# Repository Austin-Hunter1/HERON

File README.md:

# HERON

## Cloning

This repository uses git submodules. To pull everything, including submodule contents, clone with:

```bash
git clone --recurse-submodules https://github.com/Austin-Hunter1/HERON.git
```

If you already cloned without that flag, run:

```bash
git submodule update --init
```

## Submodules

- [gps-tracking-example](gps-tracking-example) — linked from [cu-sense-lab/gps-tracking-example](https://github.com/cu-sense-lab/gps-tracking-example) (upstream reference; HERON's working copy is `gnss_processing/`)
- [gnss_processing/submodules/gnss-tools](gnss_processing/submodules/gnss-tools) — linked from [cu-sense-lab/gnss-tools](https://github.com/cu-sense-lab/gnss-tools), used by `gnss_processing/`
- [HERON_WRITING](HERON_WRITING) — reports and papers, linked from [Austin-Hunter1/HERON_WRITING](https://github.com/Austin-Hunter1/HERON_WRITING)

## Where things are

- `HERON_DEPLOY_SOFTWARE/` — the flight computer and ground station software (see its `README.md`).
- `gnss_processing/` — the post-processing tools.
- `docs/` — project documents; start with `docs/GETTING_STARTED.md`.
- `SURGE/` — the 2022 predecessor project, reference only.

## GNSS Processing

[gnss_processing](gnss_processing) is HERON's own working copy of `gps-tracking-example`
(notebooks and code edits for the UAS GNSS-R tracking pipeline — reacquisition after
data-drop overflows, navigation-message decoding across a stitched run, and related
fixes) kept as a plain folder here rather than a submodule, since this project does not
have push access to `cu-sense-lab/gps-tracking-example`. See its own
[README](gnss_processing/README.md) for what differs from upstream.

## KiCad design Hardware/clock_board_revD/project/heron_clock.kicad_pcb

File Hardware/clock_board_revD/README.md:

# HERON clock board (rev D): 10 MHz + PPS distribution, jacks on the real SDR connectors

Rev D puts each jack on the SDR connector it must mate with (D-094). The rev C jacks faced the
wrong SMAs (see Q-015 b): the SDR rear edge order is **GPS ANT, 10 MHz, USB-B, PPS, DC jack**
(silkscreen on a B210 and a B200, photos 2026-10-20). The USB-B connector sits between the
10 MHz and PPS SMAs, so the board is taller and has a hole for each USB plug.

**Status: ready to order (D-101). Not ordered. Not built.** The SDR connector positions, the
USB hole size and the plug clearances are checked on the real parts (user, 2026-10-27).

The circuit, the schematic and the parts are the rev C ones, including the JST XH power
connector J1 (D-092) and the Panjit SOD-323HE land for D2 (D-093). One part change (D-097): the 10 MHz ESD diodes D4–D7 are the bidirectional TPD1E10B06DYAR
(same SOD-523 package), because the AC-coupled 10 MHz swings below GND.

## What changed from rev C

| Item | Rev C | Rev D |
| --- | --- | --- |
| Board | 118 × 44 mm, rack z 10 to 54 | 118 × 60 mm, rack z 30 to 90 |
| 10 MHz jacks J3–J6 | Faced the SDR GPS ANT SMA (wrong) | Face the SDR 10 MHz SMA (bx 34.16), rack z 43.16 |
| PPS jacks J7–J10 | Faced the SDR 10 MHz SMA (wrong) | Face the SDR PPS SMA (bx 70.89), rack z 79.89 |
| USB-B | Plug above the board | Plug through a 16 × 18 mm hole in the board; the B200_2 hole is an open notch |
| SDR GPS ANT and DC jack | GPS ANT covered by the board | Both stay free for cables: the board stays above the GPS ANT plug and below the DC plug |
| Layout | Rev B layout, patched by `make_revc.py` | New: `gen_pcb.py` places all parts and routes the sensitive nets by hand; Freerouting routes the rest (as rev B) |
| Footprints | KiCad 7 copies (25 `lib_footprint_mismatch` notes) | Loaded from the KiCad 10 library and the project library: no mismatch |
| PPS outputs | Dog-leg around a jack leg (3 starved thermals, D-091) | ESD diode and 22 R straight right of the jack tab: no starved thermals |
| 10 MHz filter columns | Right of the jack | Left of the jack (mirror image of rev C); the jack turns 180° so its tab points at the column |
| DRC | 28 items (accepted) | **0 violations, 0 unconnected, 0 footprint errors, 0 schematic parity issues** |

## Geometry

All numbers come from `revd_geom.py`. Board-local coordinates: mm, (0, 0) = top-left corner seen
from the component side (the side that faces the SDRs). Rack: world X = 46 + x, world Z = 90 − y.

| SDR | PPS jack (y 10.11) | USB hole (x0..x1, y 20.31..38.31) | 10 MHz jack (y 46.84) |
| --- | --- | --- | --- |
| B210_1 | J7 (13.16) | 11.05..27.05 | J3 (13.16) |
| B210_2 | J8 (43.16) | 41.05..57.05 | J4 (43.16) |
| B200_1 | J9 (73.16) | 71.05..87.05 | J5 (73.16) |
| B200_2 | J10 (103.16) | 101.05..118 (notch) | J6 (103.16) |

- **USB holes:** 16 mm (x) × 18 mm (y), 1 mm corner radius, centred 5.89 mm right of the jack axis
  (the USB-B axis is 5.89 mm from the SMA axis, toward the SDR component side). Sized for a generic
  straight USB 3.0 B overmold of 16 × 14 mm with 1 mm clearance. Checked with the real cable (D-101).
- **Keep-out ring:** 2 mm round each hole, on all four copper layers: no tracks, vias, pads,
  pours or parts. A hole can grow to about 20 × 22 mm by an Edge.Cuts change only.
- **Board edges:** the top edge (rack z 90) is 8.4 mm below the SDR DC jack axis (z 98.4); the
  bottom edge (z 30) is 6.8 mm above the GPS ANT axis (z 23.2). A plug up to about 13 mm in
  diameter fits on each. Checked with the real plugs (D-101).
- **Mounting holes:** 6 × M3, all 4 mm in from the long edges. H1–H4 at the corners: rack (X, Z) = (50, 86), (160, 86),
  (50, 34), (160, 34). H5, H6 (D-095) at the middle of the top and bottom edges, in line with the corner holes:
  (105, 86) and (105, 34). They carry the push of the direct-mate jacks when the SDR trays slide in. At X 105
  the rear plate is solid (between the B210_2 and B200_1 solder windows), so each standoff seats on full material.
- **J1** (JST XH): mouth on the top edge between the B210_1 and B210_2 DC plugs.
- **J2** (PPS IN, SMA): in the gap between the B200_1 and B200_2 blades, so a cable on J2 has open
  space in front of the board, as in rev C.

## Layout

- **10 MHz filter columns:** the rev C column, mirrored, on the line 7.5 mm left of each 10 MHz jack.
  The series parts are 0 R, 100 nF, 820 nH, 820 nH, 17.4 R and the last 294 R (to GND); the shunt
  parts stand beside the line (`SERIES_DY`, `SHUNTS` in `gen_pcb.py`). Each GND pad has its own via.
- **PPS outputs:** jack tab (+x) → node track → TPD1E05U06 pin 1 (GND pin below, with a via) →
  22 R lying flat, pin 2 on the node.
- **Blocks:** power input left of J8 at the top (rev C positions); LDOs under the B210_1 hole (the rev C
  block moved as one piece); TCXO U3 and LMK1C1104 U4 under the B210_2 hole; PPS buffer U6 right of J8;
  PPS input (U5, J2) between the B200 blades.
- **U3 rules (SiT5155 layout guide):** supply via → C8 pin 1 → U3 pin 9 on F.Cu; C8 pin 1 is 1.9 mm
  from pin 9 (rev C: 1.79 mm); C9 pin 1 is 2.8 mm straight under pin 9 (rev C: C9 5.5 mm from U3). A track keep-out on In2 and B.Cu stops other nets
  under U3 (checked: no other-net track under the U3 body).
- **SMP leg keep-outs:** a 4 × 4 mm no-track, no-via box round each SMP leg pad on F.Cu, In2 and B.Cu, so the
  autorouter cannot starve a leg's thermal relief.
- **Routing:** hand routes for the filter columns, the PPS chains and the U3 supply and clock. Every
  SMD GND pad gets a stub and a via. Freerouting 1.9.0 routes the other nets (the long 10 MHz feeds
  run mostly on In2, between the In1 GND plane and the B.Cu pour). Then GND pours on all four layers
  and a 2.5 mm stitching-via grid.
- **Stackup:** as rev C. In1 is solid GND. F.Cu, In2 and B.Cu have GND pours.

## Verification status

| Check | Result |
| --- | --- |
| KiCad DRC (KiCad 10.0.6, with schematic parity, 2026-10-21, with H5, H6) | 0 violations, 0 unconnected pads, 0 footprint errors, 0 parity issues |
| ERC | 0 errors, 0 warnings |
| D4–D7 to TPD1E10B06 (D-097, 2026-10-24) | Fields only: tracks and footprints unchanged. DRC 0, unconnected 0, parity 0; ERC 0 |
| Netlist (`check_net.py`) | 112 parts (with H5, H6), 51 nets. Single-node nets only on the intentional NC pins U1.4, U2.4, U5.1 |
| Rack fit (`../payload_rack/check_fit.py`, 2026-10-21, 6 standoffs) | 0 clashes. Mate report: all 8 jacks 0.000 mm radial and axial error (J3–J6 on the SDR 10 MHz SMA, J7–J10 on the PPS SMA). Stop screw access: clear |
| Rack fit, run again 2026-10-27 (after the rack changes) | 0 clashes, all 8 jacks mate, stop screw access clear |
| Gerbers compared to the board (2026-10-27) | All 16 files the same, except the date lines |
| SDR data on the real parts (user, 2026-10-27, B210 and B200) | 10 MHz SMA at 34.16, USB-B at 51.69, PPS SMA at 70.89 along the SDR edge; SMA axis 1.96 mm above the SDR board bottom face; USB hole size and GPS ANT and DC plug clearances: all correct |
| Hardware test | Not done |

## Assembly

1. **U3 SiT5155: use water-soluble flux only. Do not use no-clean flux. Do not use ultrasonic or
   megasonic cleaning.** (SiTime manufacturing guidelines.)
2. Reflow all SMD parts on the top side (`fab/heron_clock_cpl_top.csv`). D2 has the Panjit land: the
   large pad is the cathode.
3. Solder J1 (S2B-XH-A-1) and J2 (132134 SMA) by hand after reflow.
4. **J3–J10 (SMP): solder in place in the rack**, as rev C: jacks loose in their holes, board on the
   rear plate, SDRs and adapters mated, legs soldered from the back through the rear-plate windows,
   then the tabs on top. Do not move an SDR to another slot after this.
5. R23 (49.9 Ω PPS termination) is DNP. Fit it only if the GNSS PPS source needs a 50 Ω load.
6. J1 pin 1 = +5 V, pin 2 = GND. Cable side: XHP-2 housing, SXH-001T-P0.6 terminals.

## How to rebuild

Tools: KiCad 10 (its Python has `pcbnew`), Java 17 or later, Freerouting 1.9.0
(`freerouting-1.9.0.jar` from github.com/freerouting/freerouting; do not put it in git).

```bash
PATH=/Applications/KiCad/KiCad.app/Contents/MacOS:$PATH PYTHON=/Applications/KiCad/KiCad.app/Contents/Frameworks/Python.framework/Versions/Current/bin/python3 KICAD10_FOOTPRINT_DIR=/Applications/KiCad/KiCad.app/Contents/SharedSupport/footprints bash make_fab.sh
```

- `EXPORT_ONLY=1` skips `gen_pcb.py` and only makes the fab outputs from the files as they are.
  Use it after a hand edit of the PCB.
- **Freerouting can give a different route on each run.** A full rebuild changes the copper. Run
  DRC and the rack check again after a rebuild.
- KiCad 10 Python on macOS (2026-10-20): `pcbnew.ZONE_FILLER` crashes, so `kicad-cli` fills the
  zones. Do not make a `pcbnew.BOARD()` and drop it while a loaded board is in use: the next save crashes.

## Files

| Path | Content |
| --- | --- |
| `project/` | KiCad project (schematic = rev C schematic, revision D). `fab/` has the Gerber zip with drill files, BOM, Digi-Key upload, CPL, schematic and assembly PDFs, DRC and ERC reports, top and bottom renders |
| `revd_geom.py` | Board, jack and USB hole geometry, from the rack and SDR data |
| `gen_pcb.py` | Rev D placement table, hand routes, labels and silkscreen art; runs Freerouting |
| `pcbgen.py` | Board-building helpers (footprints from the netlist, tracks, vias, zones, keep-outs, GND vias, stitching, Freerouting round trip) |
| `silk_refs.py` | Reference labels (rev C script; the USB holes are keep-outs) |
| `add_center_holes.py` | Adds H5, H6 to the schematic (copies of H4 with its GND symbol; run once, idempotent) |
| `extract_logo.py`, `logo_polys.json` | The HERON logo outlines, made from `HERON/Templates and Logos/HERON_pixel_20mm.svg` (pixel rects only). Run `extract_logo.py` after each logo change |
| `update_logo.py` | Replaces only the logo polygons on the board as it is (no new route), then run `EXPORT_ONLY=1 make_fab.sh`. Last run 2026-10-24 (logo SVG with one stray pixel removed): copper, parts and texts unchanged; DRC 0, ERC 0 |
| `design.py`, `gen_sch.py`, `gen_lib.py` | Parts list as Python, schematic generator, project library (rev C, unchanged) |
| `check_net.py`, `make_bom.py`, `bom_sources.csv`, `make_fab.sh` | Netlist check, BOM, purchase data, rebuild and fab outputs |
| `sim/lpf.py` | Filter and output level model (unchanged) |
| `mockup_dxf.py`, `mockup/` | 1:1 mm DXF files for a laser-cut fit mockup: `revD_mockup_cut.dxf` (outline + pad holes), `revD_mockup_all.dxf` (layers CUT, VIAS, F_CU, B_CU), raw copper plots. Zones and loose GND stitching vias (no track) are left out so traces show. Origin = board lower-left corner, Y up, seen from the front. No kerf compensation. **Laser-ready:** `revD_laser.svg` / `.dxf` (CUT = red hairline: outline, USB holes, 6 mounting drills; ENGRAVE = solid blue fill: joined front copper, other holes are gaps; one line per edge), `revD_laser_back.*` (back copper fill). Run `python3 mockup_dxf.py` |

## Open items

- **Rear plate:** each SDR column now has a solder window and a 20 × 22 mm USB opening (PROPOSED,
  `REAR_USB_W`, `REAR_USB_H` in `heron_rack.py`). The USB cables leave through the back of the rack.
  Check the plate strength and the cable route to the NUC.
- Q-015 (a) `ADAPTER_REACH` and (d) the preload and stop design are still open. They change the rack only, not the board.
- The PPS source (GNSS receiver model) is still open.

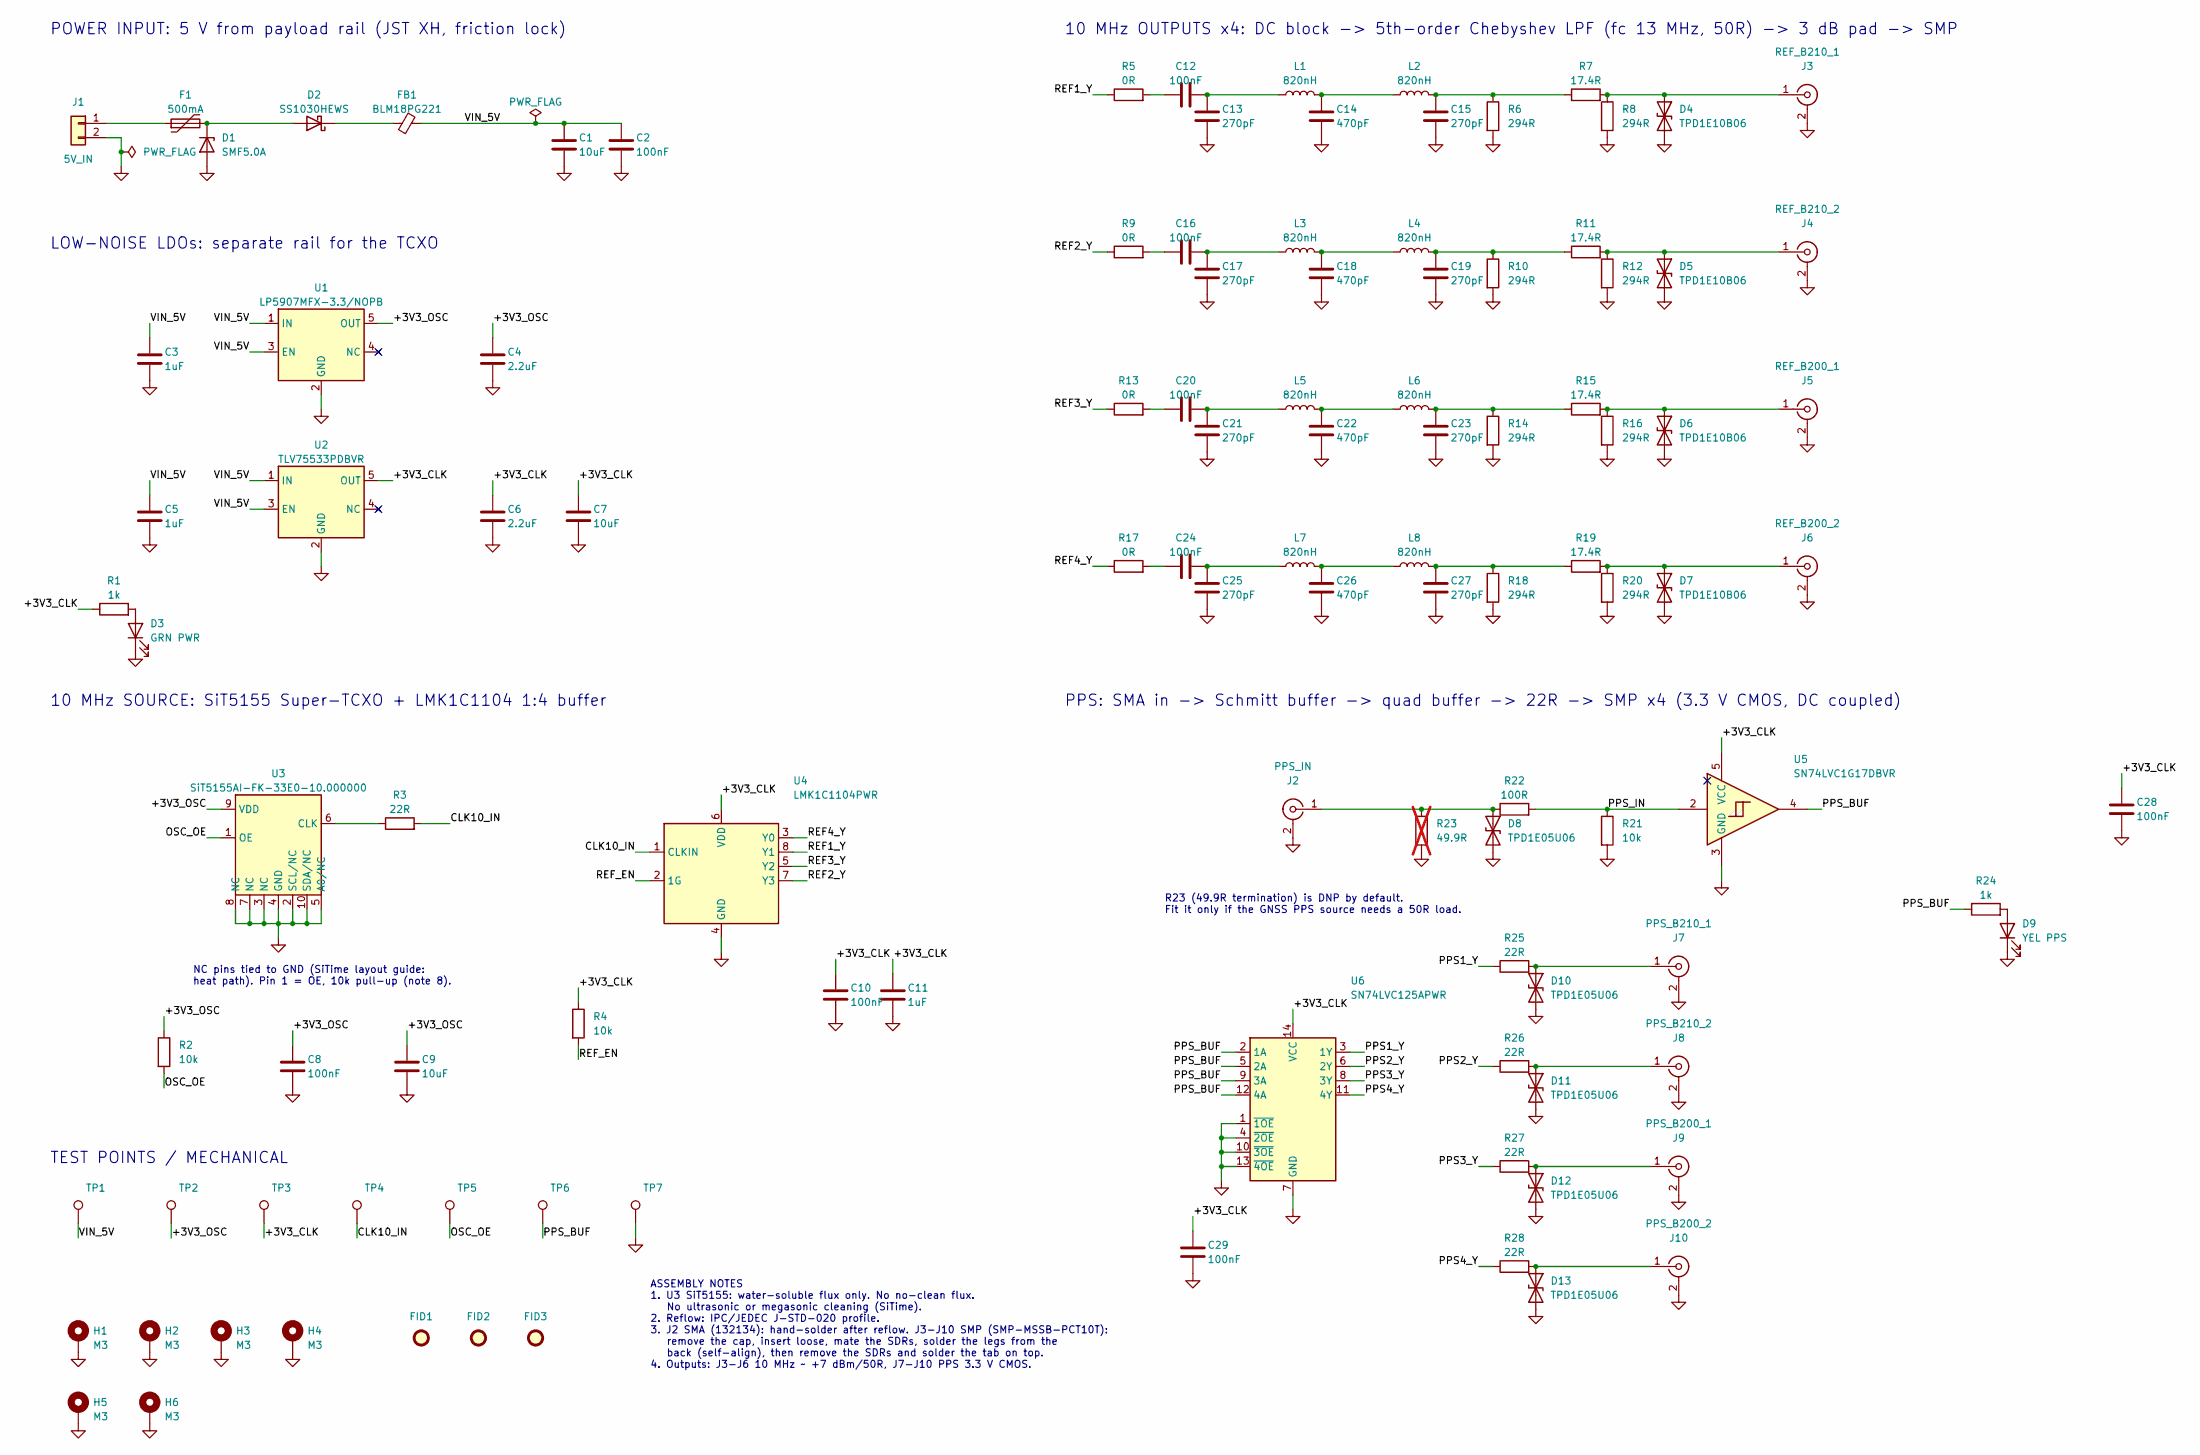
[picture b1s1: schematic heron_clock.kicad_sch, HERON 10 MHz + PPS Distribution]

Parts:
C1, C7, C9: 10uF; C_0805_2012Metric; MPN CC0805KRX5R7BB106
C2, C8, C10, C12, C16, C20, C24, C28, C29: 100nF; C_0603_1608Metric; MPN CC0603KRX7R7BB104
C3, C5, C11: 1uF; C_0603_1608Metric; MPN GRM188R61C105KA12D
C4, C6: 2.2uF; C_0603_1608Metric; MPN GRM188R6YA225KA12D
C13, C15, C17, C19, C21, C23, C25, C27: 270pF; C_0603_1608Metric; MPN GRM1885C1H271JA01D
C14, C18, C22, C26: 470pF; C_0603_1608Metric; MPN GRM1885C1H471JA01D
D1: SMF5.0A; D_SOD-123F; MPN SMF5.0A
D2: SS1030HEWS; D_SOD-323HE_Panjit; MPN SS1030HEWS_R1_00001
D3: GRN PWR; LED_0603_1608Metric; MPN 150060GS75000
D4, D5, D6, D7: TPD1E10B06; D_SOD-523; MPN TPD1E10B06DYAR
D8, D10, D11, D12, D13: TPD1E05U06; D_SOD-523; MPN TPD1E05U06DYAR
D9: YEL PPS; LED_0603_1608Metric; MPN 150060YS75000
F1: 500mA; Fuse_1206_3216Metric; MPN MF-NSMF050-2
FB1: BLM18PG221; L_0603_1608Metric; MPN BLM18PG221SN1D
FID1, FID2, FID3: Fiducial; Fiducial_1mm_Mask2mm
H1, H2, H3, H4, H5, H6: M3; MountingHole_3.2mm_M3_Pad_Via
J1: 5V_IN; JST_XH_S2B-XH-A-1_1x02_P2.50mm_Horizontal; MPN S2B-XH-A-1(LF)(SN)
J2: PPS_IN; SMA_Amphenol_132134_Vertical; MPN 132134
J3: REF_B210_1; SMP_Amphenol_SMP-MSSB-PCT10T_Vertical_Float; MPN SMP-MSSB-PCT10T
J4: REF_B210_2; SMP_Amphenol_SMP-MSSB-PCT10T_Vertical_Float; MPN SMP-MSSB-PCT10T
J5: REF_B200_1; SMP_Amphenol_SMP-MSSB-PCT10T_Vertical_Float; MPN SMP-MSSB-PCT10T
J6: REF_B200_2; SMP_Amphenol_SMP-MSSB-PCT10T_Vertical_Float; MPN SMP-MSSB-PCT10T
J7: PPS_B210_1; SMP_Amphenol_SMP-MSSB-PCT10T_Vertical_Float; MPN SMP-MSSB-PCT10T
J8: PPS_B210_2; SMP_Amphenol_SMP-MSSB-PCT10T_Vertical_Float; MPN SMP-MSSB-PCT10T
J9: PPS_B200_1; SMP_Amphenol_SMP-MSSB-PCT10T_Vertical_Float; MPN SMP-MSSB-PCT10T
J10: PPS_B200_2; SMP_Amphenol_SMP-MSSB-PCT10T_Vertical_Float; MPN SMP-MSSB-PCT10T
L1, L2, L3, L4, L5, L6, L7, L8: 820nH; L_0805_2012Metric; MPN AISC-0805-R82J-T
R1, R24: 1k; R_0603_1608Metric; Tolerance 1%; MPN RC0603FR-071KL
R2, R4, R21: 10k; R_0603_1608Metric; Tolerance 1%; MPN AC0603FR-0710KL
R3, R25, R26, R27, R28: 22R; R_0603_1608Metric; Tolerance 1%; MPN RMCF0603FT22R0
R5, R9, R13, R17: 0R; R_0603_1608Metric; Tolerance jumper; MPN RC0603JR-070RL
R6, R8, R10, R12, R14, R16, R18, R20: 294R; R_0603_1608Metric; Tolerance 1%; MPN ERJ-3EKF2940V
R7, R11, R15, R19: 17.4R; R_0603_1608Metric; Tolerance 1%; MPN RC0603FR-0717R4L
R22: 100R; R_0603_1608Metric; Tolerance 1%; MPN AC0603FR-07100RL
R23: 49.9R; R_0603_1608Metric; Tolerance 1%; MPN RC0603FR-0749R9L; not fitted
TP1: VIN_5V; TestPoint_Pad_D1.5mm
TP2: +3V3_OSC; TestPoint_Pad_D1.5mm
TP3: +3V3_CLK; TestPoint_Pad_D1.5mm
TP4: CLK10_IN; TestPoint_Pad_D1.5mm
TP5: OSC_OE; TestPoint_Pad_D1.5mm
TP6: PPS_BUF; TestPoint_Pad_D1.5mm
TP7: GND; TestPoint_Pad_D1.5mm
U1: LP5907MFX-3.3/NOPB; SOT-23-5; MPN LP5907MFX-3.3/NOPB
U2: TLV75533PDBVR; SOT-23-5; MPN TLV75533PDBVR
U3: SiT5155AI-FK-33E0-10.000000; SiTime_SiT5155_5.0x3.2mm_10L; MPN SiT5155AI-FK-33E0-10.000000
U4: LMK1C1104PWR; TSSOP-8_4.4x3mm_P0.65mm; MPN LMK1C1104PWR
U5: SN74LVC1G17DBVR; SOT-23-5; MPN SN74LVC1G17DBVR
U6: SN74LVC125APWR; TSSOP-14_4.4x5mm_P0.65mm; MPN SN74LVC125APWR

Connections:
/+3V3_CLK: C6.1, C7.1, C10.1, C11.1, C28.1, C29.1, R1.1, R4.1, TP3.1, U2.5 (OUT), U4.6 (VDD), U5.5 (VCC), U6.14 (VCC)
/+3V3_OSC: C4.1, C8.1, C9.1, R2.1, TP2.1, U1.5 (OUT), U3.9 (VDD)
/CLK10_IN: R3.2, TP4.1, U4.1 (CLKIN)
/OSC_OE: R2.2, TP5.1, U3.1 (OE)
/PPS1_Y: R25.1, U6.3 (1Y)
/PPS2_Y: R26.1, U6.6 (2Y)
/PPS3_Y: R27.1, U6.8 (3Y)
/PPS4_Y: R28.1, U6.11 (4Y)
/PPS_BUF: R24.1, TP6.1, U5.4, U6.2 (1A), U6.5 (2A), U6.9 (3A), U6.12 (4A)
/PPS_IN: R21.1, R22.2, U5.2
/REF1_Y: R5.1, U4.8 (Y1)
/REF2_Y: R9.1, U4.7 (Y3)
/REF3_Y: R13.1, U4.5 (Y2)
/REF4_Y: R17.1, U4.3 (Y0)
/REF_EN: R4.2, U4.2 (1G)
/VIN_5V: C1.1, C2.1, C3.1, C5.1, FB1.2, TP1.1, U1.1 (IN), U1.3 (EN), U2.1 (IN), U2.3 (EN)
GND: C1.2, C2.2, C3.2, C4.2, C5.2, C6.2, C7.2, C8.2, C9.2, C10.2, C11.2, C13.2, C14.2, C15.2, C17.2, C18.2, C19.2, C21.2, C22.2, C23.2, C25.2, C26.2, C27.2, C28.2, C29.2, D1.2 (A), D3.1 (K), D4.2 (A2), D5.2 (A2), D6.2 (A2), D7.2 (A2), D8.2 (A2), D9.1 (K), D10.2 (A2), D11.2 (A2), D12.2 (A2), D13.2 (A2), H1.1, H2.1, H3.1, H4.1, H5.1, H6.1, J1.2, J2.2 (Ext), J3.2 (Ext), J4.2 (Ext), J5.2 (Ext), J6.2 (Ext), J7.2 (Ext), J8.2 (Ext), J9.2 (Ext), J10.2 (Ext), R6.2, R8.2, R10.2, R12.2, R14.2, R16.2, R18.2, R20.2, R21.2, R23.2, TP7.1, U1.2 (GND), U2.2 (GND), U3.2 (SCL/NC), U3.3 (NC), U3.4 (GND), U3.5 (A0/NC), U3.7 (NC), U3.8 (NC), U3.10 (SDA/NC), U4.4 (GND), U5.3 (GND), U6.1 (~1OE), U6.4 (~2OE), U6.7 (GND), U6.10 (~3OE), U6.13 (~4OE)
unnamed: C12.1, R5.2
unnamed: C12.2, C13.1, L1.1
unnamed: C14.1, L1.2, L2.1
unnamed: C15.1, L2.2, R6.1, R7.1
unnamed: C16.1, R9.2
unnamed: C16.2, C17.1, L3.1
unnamed: C18.1, L3.2, L4.1
unnamed: C19.1, L4.2, R10.1, R11.1
unnamed: C20.1, R13.2
unnamed: C20.2, C21.1, L5.1
unnamed: C22.1, L5.2, L6.1
unnamed: C23.1, L6.2, R14.1, R15.1
unnamed: C24.1, R17.2
unnamed: C24.2, C25.1, L7.1
unnamed: C26.1, L7.2, L8.1
unnamed: C27.1, L8.2, R18.1, R19.1
unnamed: D1.1 (K), D2.2 (A), F1.2
unnamed: D2.1 (K), FB1.1
unnamed: D3.2 (A), R1.2
unnamed: D4.1 (A1), J3.1 (In), R7.2, R8.1
unnamed: D5.1 (A1), J4.1 (In), R11.2, R12.1
unnamed: D6.1 (A1), J5.1 (In), R15.2, R16.1
unnamed: D7.1 (A1), J6.1 (In), R19.2, R20.1
unnamed: D8.1 (A1), J2.1 (In), R22.1, R23.1
unnamed: D9.2 (A), R24.2
unnamed: D10.1 (A1), J7.1 (In), R25.2
unnamed: D11.1 (A1), J8.1 (In), R26.2
unnamed: D12.1 (A1), J9.1 (In), R27.2
unnamed: D13.1 (A1), J10.1 (In), R28.2
unnamed: F1.1, J1.1
unnamed: R3.1, U3.6 (CLK)

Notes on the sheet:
POWER INPUT: 5 V from payload rail (JST XH, friction lock)
PPS: SMA in -> Schmitt buffer -> quad buffer -> 22R -> SMP x4 (3.3 V CMOS, DC coupled)
NC pins tied to GND (SiTime layout guide: heat path). Pin 1 = OE, 10k pull-up (note 8).
R23 (49.9R termination) is DNP by default. Fit it only if the GNSS PPS source needs a 50R load.
TEST POINTS / MECHANICAL
10 MHz SOURCE: SiT5155 Super-TCXO + LMK1C1104 1:4 buffer
LOW-NOISE LDOs: separate rail for the TCXO
10 MHz OUTPUTS x4: DC block -> 5th-order Chebyshev LPF (fc 13 MHz, 50R) -> 3 dB pad -> SMP
ASSEMBLY NOTES 1. U3 SiT5155: water-soluble flux only. No no-clean flux. No ultrasonic or megasonic cleaning (SiTime). 2. Reflow: IPC/JEDEC J-STD-020 profile. 3. J2 SMA (132134): hand-solder after reflow. J3-J10 SMP (SMP-MSSB-PCT10T): remove the cap, insert loose, mate the SDRs, solder the legs fro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

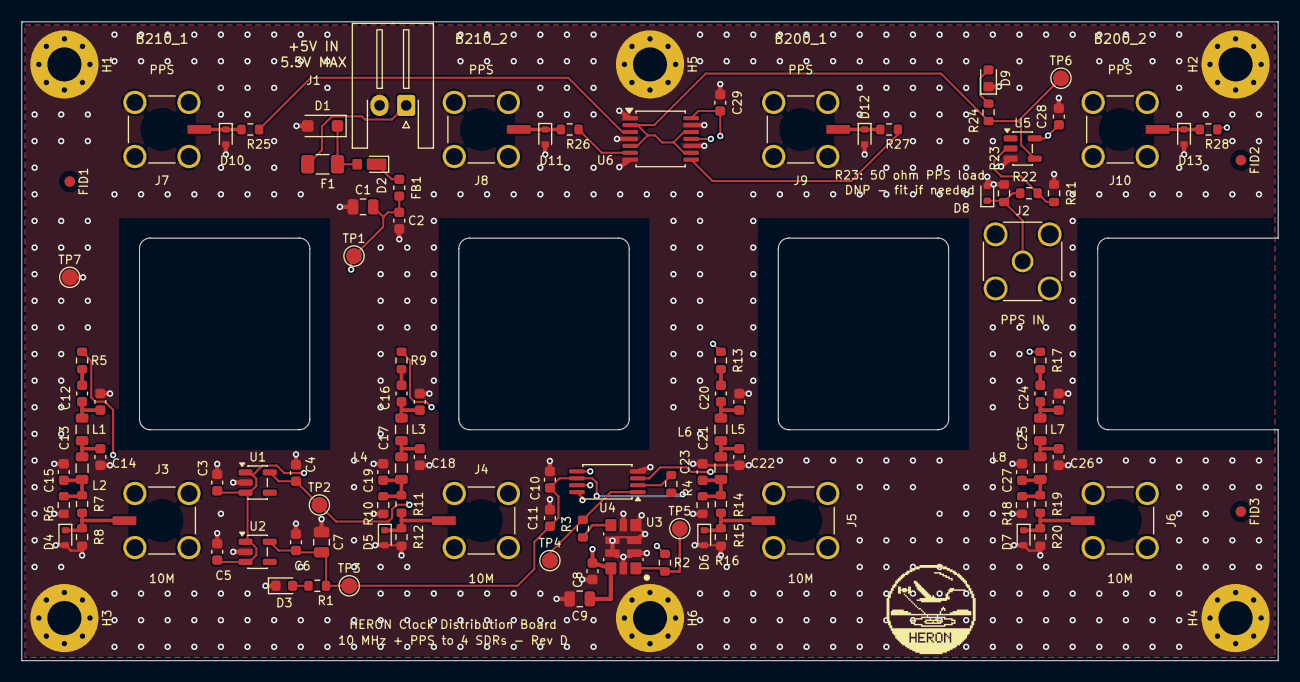
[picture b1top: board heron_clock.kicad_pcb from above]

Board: 4 copper layers, 118.0 x 60.0 mm, 112 parts (0 on the bottom side), 48 nets.

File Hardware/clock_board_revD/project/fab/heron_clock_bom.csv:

Qty,References,Value,Footprint,Manufacturer,MPN,Digi-Key PN,Dielectric,Tolerance,Fit,Stock 2026-10-05,Unit price qty 1 (USD),Note
3,C1 C7 C9,10uF,C_0805_2012Metric,YAGEO,CC0805KRX5R7BB106,311-3502-1-ND,,,Fit,523060,0.63,Replaces Murata GRM21BR61C106KE15L (no stock until 2026-11-23)
9,C2 C8 C10 C12 C16 C20 C24 C28 C29,100nF,C_0603_1608Metric,YAGEO,CC0603KRX7R7BB104,311-1088-1-ND,,,Fit,,,"Replaces Murata GRM155R71C104KA88D (no stock until 2026-12-18). Rev C (D-028): 0603, was CC0402KRX7R7BB104. Digi-Key PN, stock and price not checked yet Digi-Key PN from the team order (2026-10-20)."
3,C3 C5 C11,1uF,C_0603_1608Metric,Murata,GRM188R61C105KA12D,490-10479-1-ND,,,Fit,9932,0.11,Replaces GRM188R61C105KA93D (obsolete)
2,C4 C6,2.2uF,C_0603_1608Metric,Murata,GRM188R6YA225KA12D,490-7204-1-ND,,,Fit,66531,0.13,Replaces GRM188R61A225KE34D (obsolete); 35 V rating
8,C13 C15 C17 C19 C21 C23 C25 C27,270pF,C_0603_1608Metric,Murata,GRM1885C1H271JA01D,490-1437-1-ND,C0G,,Fit,,,"Rev C (D-028): 0603, was GRM1555C1H271JA01D. Digi-Key PN, stock and price not checked yet Digi-Key PN from the team order (2026-10-20)."
4,C14 C18 C22 C26,470pF,C_0603_1608Metric,Murata,GRM1885C1H471JA01D,490-1443-1-ND,C0G,,Fit,,,"Rev C (D-028): 0603, was GRM1555C1H471JA01D. Digi-Key PN, stock and price not checked yet Digi-Key PN from the team order (2026-10-20)."
1,D1,SMF5.0A,D_SOD-123F,Littelfuse,SMF5.0A,F5748CT-ND,,,Fit,65978,0.53,
1,D2,SS1030HEWS,D_SOD-323HE_Panjit,Panjit,SS1030HEWS_R1_00001,3757-SS1030HEWS_R1_00001CT-ND,,,Fit,6757,0.26,Replaces Nexperia PMEG3020EJ (no stock until 2027-02-16); 30 V 1 A; VERIFY land pattern
1,D3,GRN PWR,LED_0603_1608Metric,Wurth,150060GS75000,732-4971-1-ND,,,Fit,294904,0.15,
4,D4 D5 D6 D7,TPD1E10B06,D_SOD-523,Texas Instruments,TPD1E10B06DYAR,296-TPD1E10B06DYARCT-ND,,,Fit,199147 (2026-10-24),0.55,D-045: bidirectional ESD on the 10 MHz outputs D4-D7 (replaces TPD1E05U06DYAR there). Same DYA (SOD-523) package. Stock and price checked on Digi-Key 2026-10-24.
5,D8 D10 D11 D12 D13,TPD1E05U06,D_SOD-523,Texas Instruments,TPD1E05U06DYAR,296-TPD1E05U06DYARCT-ND,,,Fit,,,"Rev C (D-028): SOD-523 (DYA), was TPD1E05U06DPYR. Digi-Key PN, stock and price not checked yet Digi-Key PN from the team order (2026-10-20)."
1,D9,YEL PPS,LED_0603_1608Metric,Wurth,150060YS75000,732-4981-1-ND,,,Fit,110706,0.15,
1,F1,500mA,Fuse_1206_3216Metric,Bourns,MF-NSMF050-2,MF-NSMF050-2CT-ND,,,Fit,29689,0.40,
1,FB1,BLM18PG221,L_0603_1608Metric,Murata,BLM18PG221SN1D,490-5221-1-ND,,,Fit,273730,0.14,
1,J1,5V_IN,JST_XH_S2B-XH-A-1_1x02_P2.50mm_Horizontal,JST,S2B-XH-A-1(LF)(SN),455-S2B-XH-A-1-ND,,,Fit,9411,0.15,"J1, through-hole. Replaces SM02B-GHS-TB(LF)(SN) (out of stock at Digi-Key until 2026-11-16) (D-040). Stock checked 2026-10-20. Mating housing XHP-2 and crimp terminals SXH-001T-P0.6 (cable side) are not in this BOM"
1,J2,PPS_IN,SMA_Amphenol_132134_Vertical,Amphenol RF,132134,ACX1230-ND,,,Fit,23072,7.30,
8,J3 J4 J5 J6 J7 J8 J9 J10,PPS_B200_1 / PPS_B200_2 / PPS_B210_1 / PPS_B210_2 / REF_B200_1 / REF_B200_2 / REF_B210_1 / REF_B210_2,SMP_Amphenol_SMP-MSSB-PCT10T_Vertical_Float,Amphenol RF,SMP-MSSB-PCT10T,115-SMP-MSSB-PCT10TCT-ND,,,Fit,407,6.89,"Smooth bore, THT legs + SMD signal tab (2026-10-07). Was SMP-MSSB-PCT ($29.11). Remove the pick-and-place cap before mating. Stock checked 2026-10-07"
8,L1 L2 L3 L4 L5 L6 L7 L8,820nH,L_0805_2012Metric,Abracon,AISC-0805-R82J-T,535-10512-1-ND,,,Fit,14360,0.42,"Replaces Coilcraft 0805CS-821XJRC (Digi-Key Marketplace only). Same size, ceramic core, 2.3 ohm, Q 23 @ 50 MHz, SRF 250 MHz. Stock checked 2026-10-07"
2,R1 R24,1k,R_0603_1608Metric,YAGEO,RC0603FR-071KL,311-1.00KHRCT-ND,,1%,Fit,,,"Rev C (D-028): 0603, was RC0402FR-071KL. Digi-Key PN, stock and price not checked yet Digi-Key PN from the team order (2026-10-20)."
3,R2 R4 R21,10k,R_0603_1608Metric,YAGEO,AC0603FR-0710KL,311-10KLDCT-ND,,1%,Fit,,0.03,"Rev C (D-028): 0603, was RC0402FR-0710KL. AC series (AEC-Q200) in place of RC series (D-036). Price from the cart of 2026-10-15; stock not checked"
5,R3 R25 R26 R27 R28,22R,R_0603_1608Metric,Stackpole Electronics Inc,RMCF0603FT22R0,RMCF0603FT22R0CT-ND,,1%,Fit,,,"Rev C (D-028): 0603, was RC0402FR-0722RL. YAGEO RC0603FR-0722RL out of stock on 2026-10-07: Stackpole used. In stock in the 2026-10-07 Digi-Key cart (0.021 USD at qty 10)"
4,R5 R9 R13 R17,0R,R_0603_1608Metric,YAGEO,RC0603JR-070RL,311-0.0GRCT-ND,,jumper,Fit,,,"Rev C (D-028): 0603, was RC0402JR-070RL. Digi-Key PN, stock and price not checked yet Digi-Key PN from the team order (2026-10-20)."
8,R6 R8 R10 R12 R14 R16 R18 R20,294R,R_0603_1608Metric,Panasonic,ERJ-3EKF2940V,P294HCT-ND,,1%,Fit,,,"Rev C (D-028): 0603, was ERJ-2RKF2940X. Digi-Key PN, stock and price not checked yet Digi-Key PN from the team order (2026-10-20)."
4,R7 R11 R15 R19,17.4R,R_0603_1608Metric,YAGEO,RC0603FR-0717R4L,311-17.4HRCT-ND,,1%,Fit,,,"Rev C (D-028): 0603, was RC0402FR-0717R4L. Digi-Key PN, stock and price not checked yet Digi-Key PN from the team order (2026-10-20)."
1,R22,100R,R_0603_1608Metric,YAGEO,AC0603FR-07100RL,YAG3561CT-ND,,1%,Fit,,0.028,"Rev C (D-028): 0603, was RC0402FR-07100RL. AC series (AEC-Q200) in place of RC series (D-036). Price from the cart of 2026-10-15; stock not checked"
1,U1,LP5907MFX-3.3/NOPB,SOT-23-5,Texas Instruments,LP5907MFX-3.3/NOPB,296-38557-1-ND,,,Fit,,,U1 (+3V3_OSC). Replaces TPS7A2033PDBVR (no stock until 2026-11-23). Stock not checked yet
1,U2,TLV75533PDBVR,SOT-23-5,Texas Instruments,TLV75533PDBVR,296-50411-1-ND,,,Fit,,,U2 (+3V3_CLK). Replaces TPS7A2033PDBVR (no stock until 2026-11-23). Stock not checked yet
1,U3,SiT5155AI-FK-33E0-10.000000,SiTime_SiT5155_5.0x3.2mm_10L,SiTime,SiT5155AI-FK-33E0-10.000000,,,,Fit,0,55.66,In hand (2026-10-07). Digi-Key estimate 2027-05-17 if more are needed
1,U4,LMK1C1104PWR,TSSOP-8_4.4x3mm_P0.65mm,Texas Instruments,LMK1C1104PWR,296-LMK1C1104PWRCT-ND,,,Fit,2216,3.75,
1,U5,SN74LVC1G17DBVR,SOT-23-5,Texas Instruments,SN74LVC1G17DBVR,296-11933-1-ND,,,Fit,260074,0.15,
1,U6,SN74LVC125APWR,TSSOP-14_4.4x5mm_P0.65mm,Texas Instruments,SN74LVC125APWR,296-1222-1-ND,,,Fit,19070,0.41,
1,R23,49.9R,R_0603_1608Metric,YAGEO,RC0603FR-0749R9L,311-49.9HRCT-ND,,1%,DNP,,,"R23 is DNP (fit only if the GNSS PPS source needs 50 ohm). 5 spares in the Digi-Key upload. Rev C (D-028): 0603, was RC0402FR-0749R9L. Digi-Key PN, stock and price not checked yet Digi-Key PN from the team order (2026-10-20)."
8,(off-board),"Adapter SMA plug to SMP female, one on each SDR rear 10 MHz and PPS SMA; plugs directly onto J3-J10",,Cinch Connectivity Solutions Johnson,134-1019-451,24-134-1019-451-ND,,,Off-board,71,33.83,"One-piece adapter, no bullet (D-027, 2026-10-07). 14.25 mm long. Stock checked 2026-10-07. 10+ price 28.75"
